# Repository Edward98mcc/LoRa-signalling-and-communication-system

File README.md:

# LoRa Signalling and Communication System for Events

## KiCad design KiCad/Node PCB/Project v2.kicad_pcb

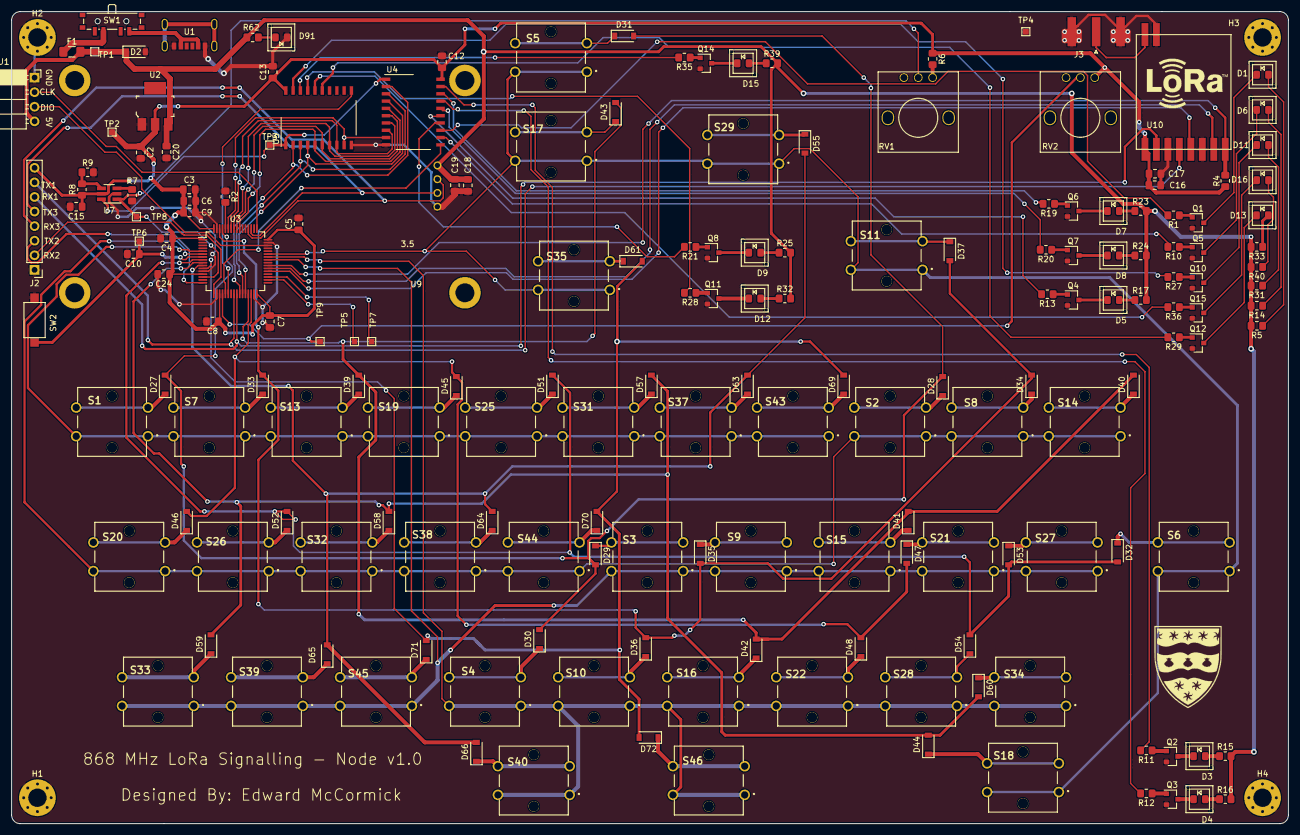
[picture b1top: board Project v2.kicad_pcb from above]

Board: 2 copper layers, 222.5 x 141.5 mm, 186 parts (0 on the bottom side), 142 nets.

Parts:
C2, C20: 10u; C_0805_2012Metric_Pad1.18x1.45mm_HandSolder
C3, C19: 4u7; C_0805_2012Metric_Pad1.18x1.45mm_HandSolder
C4, C5, C6, C7, C8, C9, C10, C12, C13, C15, C16, C18: 100n; C_0805_2012Metric_Pad1.18x1.45mm_HandSolder
C17, C24: 10n; C_0805_2012Metric_Pad1.18x1.45mm_HandSolder
D1, D6, D9, D11: Red; VLP-350-R
D2, D27, D28, D29, D30, D31, D32, D33, D34, D35, D36, D37, D39, D40, D41, D42, D43, D44, D45, D46, D47, D48, D51, D52, D53, D54, D55, D57, D58, D59, D60, D61, D63, D64, D65, D66, D69, D70, D71, D72: D_Small; D_SOD-123
D3, D7: Yellow; VLP-350-R
D4, D5, D8: Green; VLP-350-R
D12, D13, D15, D16: Blue; VLP-350-R
D91: LED_Small; VLP-350-R
F1: 350mA; Fuse_1206_3216Metric_Pad1.42x1.75mm_HandSolder
H1, H2, H3, H4: MountingHole_Pad; MountingHole_3.2mm_M3_Pad_Via
J1: 0022232041; PinSocket_1x04_P2.54mm_Horizontal
J2: Conn_01x08; PinHeader_1x08_P2.54mm_Vertical
J3: CONSMA001-SMD-G; SMA_Amphenol_132289_EdgeMount
Q1, Q2, Q3, Q4, Q5, Q6, Q7, Q8, Q10, Q11, Q12, Q14, Q15: Q_NPN_BEC; SOT-23
R1, R10, R11, R12, R13, R19, R20, R21, R27, R28, R29, R32, R33, R35, R36, R39, R40: 4k7; R_0805_2012Metric_Pad1.20x1.40mm_HandSolder
R2, R4: 10k; R_0805_2012Metric_Pad1.20x1.40mm_HandSolder
R5, R14, R15, R23, R25, R31, R62: 1k; R_0805_2012Metric_Pad1.20x1.40mm_HandSolder
R6: 25k; R_0805_2012Metric_Pad1.20x1.40mm_HandSolder
R7: 200k; R_0805_2012Metric_Pad1.20x1.40mm_HandSolder
R8: 1000k; R_0805_2012Metric_Pad1.20x1.40mm_HandSolder
R9: 523k; R_0805_2012Metric_Pad1.20x1.40mm_HandSolder
R16, R17, R24: 470; R_0805_2012Metric_Pad1.20x1.40mm_HandSolder
RV1, RV2: 10k; B103
S1: Q / 1; B3F-4000
S2: O / 8; B3F-4000
S3: H / £; B3F-4000
S4: V; B3F-4000
S5: Up; B3F-4000
S6: Back; B3F-4000
S7: W / 2; B3F-4000
S8: P / 9; B3F-4000
S9: J / $; B3F-4000
S10: B; B3F-4000
S11: Ready; B3F-4000
S13: E / 3; B3F-4000
S14: ? / 0; B3F-4000
S15: K / %; B3F-4000
S16: N; B3F-4000
S17: Down; B3F-4000
S18: Caps Lock / Shift; B3F-4000
S19: R / 4; B3F-4000
S20: A / -; B3F-4000
S21: L / ^; B3F-4000
S22: M; B3F-4000
S25: T / 5; B3F-4000
S26: S / =; B3F-4000
S27: : / &; B3F-4000
S28: < / ,; B3F-4000
S29: Acknowledge; B3F-4000
S31: Y / 6; B3F-4000
S32: D / +; B3F-4000
S33: Z / *; B3F-4000
S34: > / .; B3F-4000
S35: Send; B3F-4000
S37: U / 7; B3F-4000
S38: F / !; B3F-4000
S39: X / (; B3F-4000
S40: Space 1; B3F-4000
S43: I / 8; B3F-4000
S44: G / "; B3F-4000
S45: C / ); B3F-4000
S46: Space 2; B3F-4000
SW1: SW_SP3T; SW_SP3T_PCM13
SW2: SW_SPST; SW_SPST_CK_RS282G05A3
TP1, TP2, TP3, TP4, TP5, TP6, TP7, TP8, TP9: TestPoint; TestPoint_Pad_1.0x1.0mm
U1: USBC-C456012; USB_TypeC
U2: NCP1117ST33T3G; SOT-223
U3: STM32F303RETx; LQFP-64_10x10mm_P0.5mm
U4, U5: 74LS573; SO-20_12.8x7.5mm_P1.27mm
U7: LTC6992-1; SOT-23-6_Handsoldering
U9: 3.5; 2.4-Nextion
U10: HM-TRLR-S-868; HM-TRLR-S-868_v2

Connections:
+3V3: C2.1, C3.1, C4.1, C5.1, C6.1, C7.1, C8.1, C9.1, C12.1, C13.1, C15.1, C16.1, C17.1, C24.1, J2.8, R4.2, R6.1, R8.1, RV2.1, TP2.1, U2.2, U3.1, U3.13, U3.19, U3.32, U3.48, U3.64, U4.20, U5.20, U7.5, U10.1
+5V: C18.1, C19.1, C20.1, D2.1, F1.2, J1.4, R5.2, R14.2, R15.2, R16.2, R17.2, R23.2, R24.2, R25.2, R31.2, R32.2, R33.2, R39.2, R40.2, R62.1, TP1.1, U2.3, U9.4
+5VL: SW1.1, U1.2
Column1: D27.2, D28.2, D29.2, D30.2, D31.2, U3.61
Column2: D33.2, D34.2, D35.2, D36.2, D37.2, U3.62
Column3: D39.2, D40.2, D41.2, D42.2, D43.2, U3.29
Column4: D45.2, D46.2, D47.2, D48.2, U3.30
Column5: D32.2, D51.2, D52.2, D53.2, D54.2, U3.8
Column6: D44.2, D57.2, D58.2, D59.2, D60.2, U3.9
Column7: D55.2, D63.2, D64.2, D65.2, D66.2, U3.10
Column8: D61.2, D69.2, D70.2, D71.2, D72.2, U3.11
GND: C2.2, C3.2, C4.2, C5.2, C6.2, C7.2, C8.2, C9.2, C10.2, C12.2, C13.2, C15.2, C16.2, C17.2, C18.2, C19.2, C20.2, C24.2, D2.2, D91.1, H1.1, H2.1, H3.1, H4.1, J1.1, J2.1, J3.2, Q1.2, Q2.2, Q3.2, Q4.2, Q5.2, Q6.2, Q7.2, Q8.2, Q10.2, Q11.2, Q12.2, Q14.2, Q15.2, R2.1, R7.2, R9.2, RV1.3, RV2.3, SW2.2, TP4.1, U1.1, U2.1, U3.12, U3.18, U3.31, U3.47, U3.63, U4.10, U5.10, U7.2, U9.1, U10.3, U10.6, U10.10
LED_Dim: RV1.2, TP8.1, U3.14, U7.1
LE_1: U3.21, U4.11
LE_2: U3.22, U5.11
LORA_Config: U3.37, U10.5
LORA_Reset: R4.1, U3.39, U10.8
LORA_Status: U3.38, U10.7
LP0: U3.26, U4.2, U5.2
LP1: U3.27, U4.3, U5.3
LP2: U3.28, U4.4, U5.4
LP3: U3.55, U4.5, U5.5
LP4: U3.56, U4.6, U5.6
LP5: U3.57, U4.7, U5.7
LP6: U3.58, U4.8, U5.8
LP7: U3.59, U4.9, U5.9
Latch1Out0: R11.2, U4.19
Latch1Out1: R19.2, U4.18
Latch1Out2: R12.2, U4.17
Latch1Out3: R20.2, U4.16
Latch1Out4: R13.2, U4.15
Latch1Out5: R21.2, U4.14
Latch1Out6: R1.2, U4.13
Latch1Out7: R10.2, U4.12
Latch2Out0: R27.2, U5.19
Latch2Out1: R35.2, U5.18
Latch2Out2: R28.2, U5.17
Latch2Out3: R36.2, U5.16
Latch2Out4: R29.2, U5.15
NRST: C10.1, SW2.1, TP6.1, U3.7
unnamed: D1.1, Q1.3
unnamed: D1.2, R5.1
unnamed: D3.1, Q2.3
unnamed: D3.2, R15.1
unnamed: D4.1, Q3.3
unnamed: D4.2, R16.1
unnamed: D5.1, Q4.3
unnamed: D5.2, R17.1
unnamed: D6.1, Q5.3
unnamed: D6.2, R14.1
unnamed: D7.1, Q6.3
unnamed: D7.2, R23.1
unnamed: D8.1, Q7.3
unnamed: D8.2, R24.1
unnamed: D9.1, Q8.3
unnamed: D9.2, R25.1
unnamed: D11.1, Q10.3
unnamed: D11.2, R31.1
unnamed: D12.1, Q11.3
unnamed: D12.2, R32.1
unnamed: D13.1, Q12.3
unnamed: D13.2, R33.1
unnamed: D15.1, Q14.3
unnamed: D15.2, R39.1
unnamed: D16.1, Q15.3
unnamed: D16.2, R40.1
unnamed: D27.1, S1.3, S1.4
unnamed: D28.1, S2.3, S2.4
unnamed: D29.1, S3.3, S3.4
unnamed: D30.1, S4.3, S4.4
unnamed: D31.1, S5.3, S5.4
unnamed: D32.1, S6.3, S6.4
unnamed: D33.1, S7.3, S7.4
unnamed: D34.1, S8.3, S8.4
unnamed: D35.1, S9.3, S9.4
unnamed: D36.1, S10.3, S10.4
unnamed: D37.1, S11.3, S11.4
unnamed: D39.1, S13.3, S13.4
unnamed: D40.1, S14.3, S14.4
unnamed: D41.1, S15.3, S15.4
unnamed: D42.1, S16.3, S16.4
unnamed: D43.1, S17.3, S17.4
unnamed: D44.1, S18.3, S18.4
unnamed: D45.1, S19.3, S19.4
unnamed: D46.1, S20.3, S20.4
unnamed: D47.1, S21.3, S21.4
unnamed: D48.1, S22.3, S22.4
unnamed: D51.1, S25.3, S25.4
unnamed: D52.1, S26.3, S26.4
unnamed: D53.1, S27.3, S27.4
unnamed: D54.1, S28.3, S28.4
unnamed: D55.1, S29.3, S29.4
unnamed: D57.1, S31.3, S31.4
unnamed: D58.1, S32.3, S32.4
unnamed: D59.1, S33.3, S33.4
unnamed: D60.1, S34.3, S34.4
unnamed: D61.1, S35.3, S35.4
unnamed: D63.1, S37.3, S37.4
unnamed: D64.1, S38.3, S38.4
unnamed: D65.1, S39.3, S39.4
unnamed: D66.1, S40.3, S40.4
unnamed: D69.1, S43.3, S43.4
unnamed: D70.1, S44.3, S44.4
unnamed: D71.1, S45.3, S45.4
unnamed: D72.1, S46.3, S46.4
unnamed: D91.2, R62.2
unnamed: F1.1, SW1.3
unnamed: J3.1, U10.9
unnamed: Q1.1, R1.1
unnamed: Q2.1, R11.1
unnamed: Q3.1, R12.1
unnamed: Q4.1, R13.1
unnamed: Q5.1, R10.1
unnamed: Q6.1, R19.1
unnamed: Q7.1, R20.1
unnamed: Q8.1, R21.1
unnamed: Q10.1, R27.1
unnamed: Q11.1, R28.1
unnamed: Q12.1, R29.1
unnamed: Q14.1, R35.1
unnamed: Q15.1, R36.1
unnamed: R2.2, U3.60
unnamed: R6.2, RV1.1
unnamed: R7.1, U7.3
unnamed: R8.2, R9.1, U7.4
PWM_Out: TP3.1, U4.1, U5.1, U7.6
ROW_1: S1.1, S1.2, S7.1, S7.2, S13.1, S13.2, S19.1, S19.2, S25.1, S25.2, S31.1, S31.2, S37.1, S37.2, S43.1, S43.2, U3.5
ROW_2: S2.1, S2.2, S8.1, S8.2, S14.1, S14.2, S20.1, S20.2, S26.1, S26.2, S32.1, S32.2, S38.1, S38.2, S44.1, S44.2, U3.6
ROW_3: S3.1, S3.2, S9.1, S9.2, S15.1, S15.2, S21.1, S21.2, S27.1, S27.2, S33.1, S33.2, S39.1, S39.2, S45.1, S45.2, U3.41
ROW_4: S4.1, S4.2, S10.1, S10.2, S16.1, S16.2, S22.1, S22.2, S28.1, S28.2, S34.1, S34.2, S40.1, S40.2, S46.1, S46.2, U3.42
ROW_5: S5.1, S5.2, S6.1, S6.2, S11.1, S11.2, S17.1, S17.2, S18.1, S18.2, S29.1, S29.2, S35.1, S35.2, U3.43
SWCLK: J1.2, U3.49
SWDIO: J1.3, U3.46
Screen_Dim: RV2.2, TP9.1, U3.20
Spare1: TP5.1, U3.34
Spare2: TP7.1, U3.35
USART1_RX: J2.6, U3.25, U10.2
USART1_TX: J2.7, U3.24, U10.4
USART2_RX: J2.2, U3.17
USART2_TX: J2.3, U3.16
USART3_RX: J2.4, U3.52, U9.3
USART3_TX: J2.5, U3.51, U9.2

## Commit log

2021-04-18 Add readme
